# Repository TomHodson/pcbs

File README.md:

# PCB Designs
A place to store Kicad PCB designs.

### USB PSU Carrier Board

Kicad Images rendered with [this handy action](https://github.com/linalinn/kicad-render/tree/main).

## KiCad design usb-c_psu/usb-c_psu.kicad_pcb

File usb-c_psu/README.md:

## USB PSU Carrier Board

## Todo
* add enable mosfets with led indicator for each channel
* make each channel a parametrised sub-schematic?
* Figure out how to copy the layout for each channel down the board
* Figure out exactly how wide the board can be and still fit in the case
* add decoupling caps for the ina219s
* Add solderable jumper footprints for the address select, one that's one by default

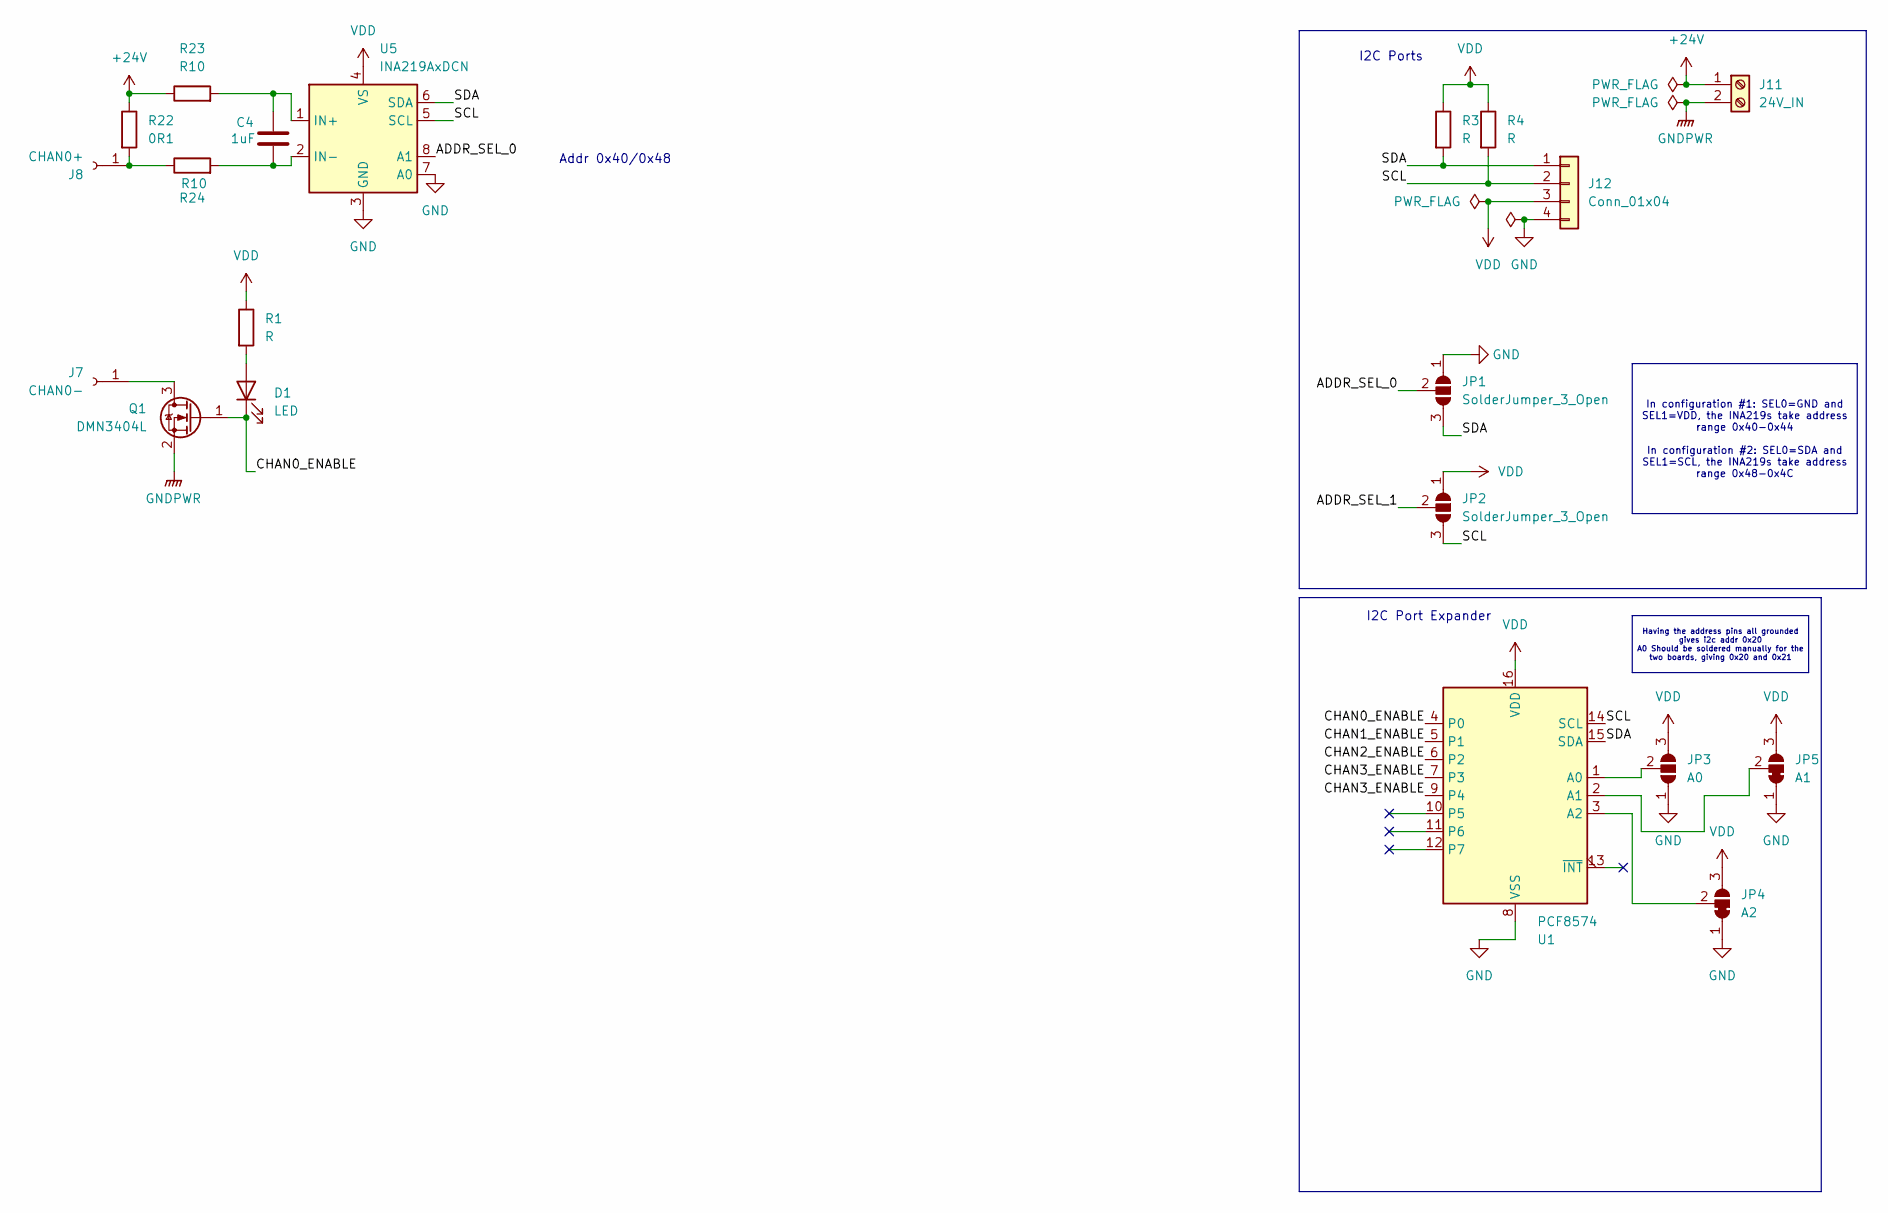
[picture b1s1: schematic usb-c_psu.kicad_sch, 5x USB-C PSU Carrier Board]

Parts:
C4: 1uF; C_0603_1608Metric
D1: LED; LED_0402_1005Metric
J7: CHAN0-; SolderWire-0.5sqmm_1x01_D0.9mm_OD2.1mm
J8: CHAN0+; SolderWire-0.5sqmm_1x01_D0.9mm_OD2.1mm
J11: 24V_IN; TerminalBlock_4Ucon_1x02_P3.50mm_Horizontal
J12: Conn_01x04; JST_ZH_B4B-ZR_1x04_P1.50mm_Vertical
JP1, JP2: SolderJumper_3_Open; SolderJumper-3_P1.3mm_Open_RoundedPad1.0x1.5mm_NumberLabels
JP3: A0; SolderJumper-3_P1.3mm_Open_RoundedPad1.0x1.5mm_NumberLabels
JP4: A2; SolderJumper-3_P1.3mm_Bridged12_Pad1.0x1.5mm_NumberLabels
JP5: A1; SolderJumper-3_P1.3mm_Bridged12_Pad1.0x1.5mm_NumberLabels
Q1: DMN3404L; SOT-23
R1: R
R3, R4: R; R_0402_1005Metric_Pad0.72x0.64mm_HandSolder
R22: 0R1; R_1210_3225Metric_Pad1.30x2.65mm_HandSolder
R23, R24: R10; R_0402_1005Metric
U1: PCF8574; SOIC-16W_7.5x10.3mm_P1.27mm
U5: INA219AxDCN; SOT-23-8

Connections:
+24V: J11.1, R22.1, R23.1
/ADDR_SEL_0: JP1.2 (C), U5.8 (A1)
/ADDR_SEL_1: JP2.2 (C)
/CHAN0_ENABLE: D1.1 (K), Q1.1 (G), U1.4 (P0)
/CHAN1_ENABLE: U1.5 (P1)
/CHAN2_ENABLE: U1.6 (P2)
/CHAN3_ENABLE: U1.7 (P3), U1.9 (P4)
/SCL: J12.2, JP2.3 (B), R4.2, U1.14 (SCL), U5.5 (SCL)
/SDA: J12.1, JP1.3 (B), R3.2, U1.15 (SDA), U5.6 (SDA)
GND: J12.4, JP1.1 (A), JP3.1 (A), JP4.1 (A), JP5.1 (A), U1.8 (VSS), U5.3 (GND), U5.7 (A0)
GNDPWR: J11.2, Q1.2 (S)
unnamed: D1.2 (A), R1.2
unnamed: J7.1, Q1.3 (D)
unnamed: J8.1, R22.2, R24.1
unnamed: JP3.2 (C), U1.1 (A0)
unnamed: JP4.2 (C), U1.3 (A2)
unnamed: JP5.2 (C), U1.2 (A1)
unnamed: C4.1, R23.2, U5.1 (IN+)
unnamed: C4.2, R24.2, U5.2 (IN-)
VDD: J12.3, JP2.1 (A), JP3.3 (B), JP4.3 (B), JP5.3 (B), R1.1, R3.1, R4.1, U1.16 (VDD), U5.4 (VS)

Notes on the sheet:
In configuration #1: SEL0=GND and SEL1=VDD, the INA219s take address range 0x40-0x44 In configuration #2: SEL0=SDA and SEL1=SCL, the INA219s take address range 0x48-0x4C
Having the address pins all grounded gives i2c addr 0x20 A0 Should be soldered manually for the two boards, giving 0x20 and 0x21
I2C Ports
Addr 0x40/0x48
I2C Port Expander

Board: 2 copper layers, 19 parts (3 on the bottom side), 16 nets, no tracks yet.

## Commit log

2024-08-24 Initial test of image generation
2024-08-24 change path
2024-08-24 Update on clause
2024-08-25 Rename
2024-08-26 Add animation
2024-08-30 Remove autosave files
2024-08-30 update connector footprints
